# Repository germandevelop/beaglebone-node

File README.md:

# beaglebone-node
## Build
### Release ###
```
mkdir ./build
cd ./build
cmake ..
make all
```
### Debug ###
```
mkdir ./build
cd ./build
cmake -DCMAKE_BUILD_TYPE=Debug ..
make all
```
## Build tests
### Build ###
```
mkdir ./build
cd ./build
cmake -DCMAKE_BUILD_TYPE=Debug -DBUILD_TESTS=ON ..
make tests
```
### Run ###
```
make test
```

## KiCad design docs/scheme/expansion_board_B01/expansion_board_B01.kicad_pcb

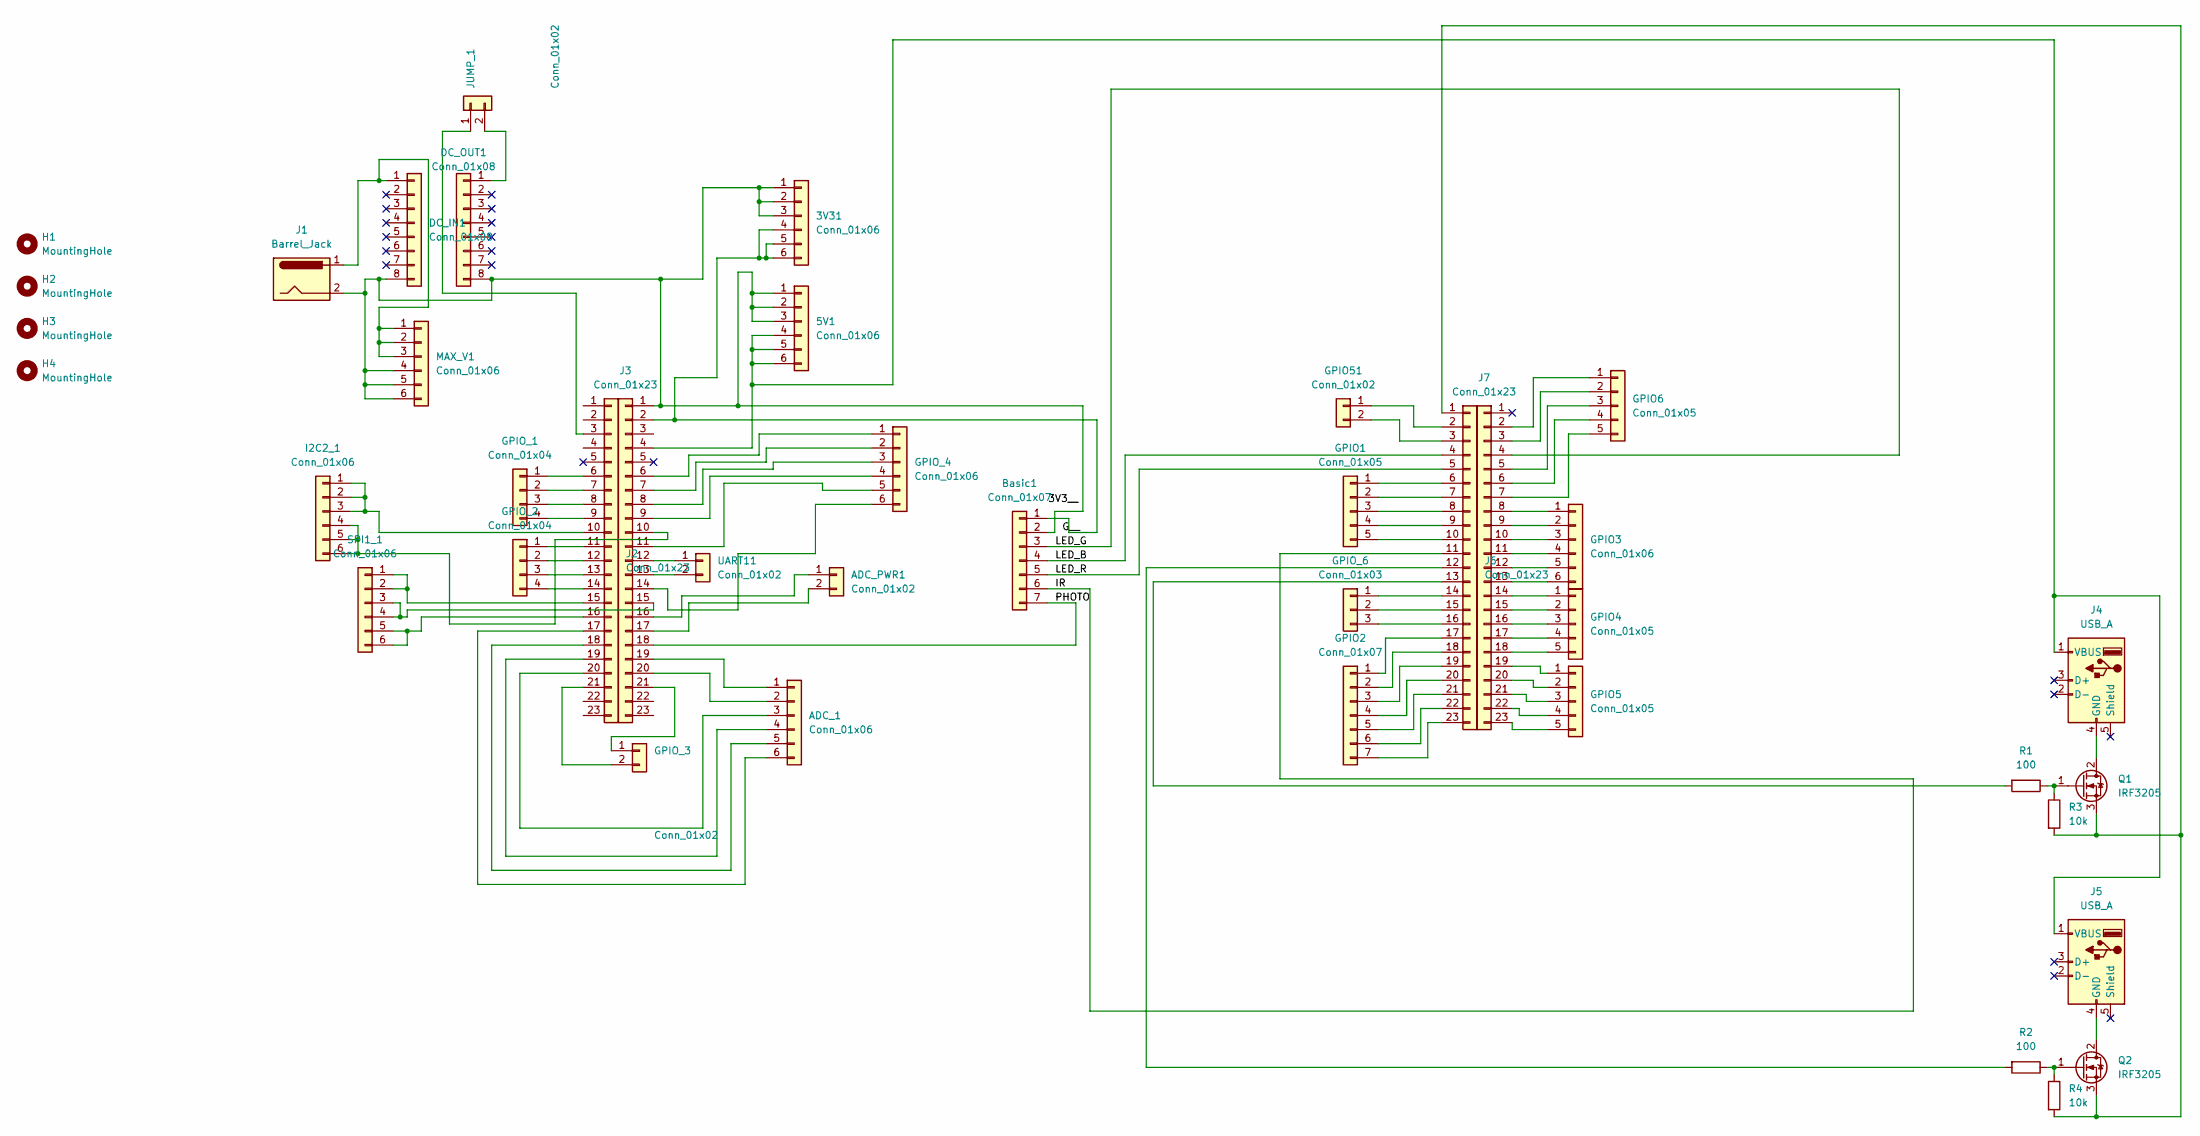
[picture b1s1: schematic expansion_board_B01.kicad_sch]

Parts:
3V31, 5V1: Conn_01x06; PinHeader_1x06_P2.54mm_Vertical
ADC_1: Conn_01x06; PinHeader_1x06_P2.54mm_Vertical
ADC_PWR1: Conn_01x02; PinHeader_1x02_P2.54mm_Vertical
Basic1: Conn_01x07; PinHeader_1x07_P2.54mm_Vertical
DC_IN1: Conn_01x08; PinHeader_1x08_P2.54mm_Vertical
DC_OUT1: Conn_01x08; PinHeader_1x08_P2.54mm_Vertical
GPIO1, GPIO4, GPIO5, GPIO6: Conn_01x05; PinHeader_1x05_P2.54mm_Vertical
GPIO2: Conn_01x07; PinHeader_1x07_P2.54mm_Vertical
GPIO3: Conn_01x06; PinHeader_1x06_P2.54mm_Vertical
GPIO51: Conn_01x02; PinHeader_1x02_P2.54mm_Vertical
GPIO_1, GPIO_2: Conn_01x04; PinHeader_1x04_P2.54mm_Vertical
GPIO_3: Conn_01x02; PinHeader_1x02_P2.54mm_Vertical
GPIO_4: Conn_01x06; PinHeader_1x06_P2.54mm_Vertical
GPIO_6: Conn_01x03; PinHeader_1x03_P2.54mm_Vertical
H1, H2, H3, H4: MountingHole; MountingHole_2.5mm_Pad
I2C2_1: Conn_01x06; PinHeader_1x06_P2.54mm_Vertical
J1: Barrel_Jack; BarrelJack_Horizontal
J2, J3, J6, J7: Conn_01x23; PinHeader_1x23_P2.54mm_Vertical
J4, J5: USB_A; USB_A_CONNFLY_DS1095-WNR0
JUMP_1: Conn_01x02; PinHeader_1x02_P2.54mm_Vertical
MAX_V1: Conn_01x06; PinHeader_1x06_P2.54mm_Vertical
Q1, Q2: IRF3205; TO-220-3_Vertical
R1, R2: 100; R_Axial_DIN0207_L6.3mm_D2.5mm_P10.16mm_Horizontal
R3, R4: 10k; R_Axial_DIN0207_L6.3mm_D2.5mm_P10.16mm_Horizontal
SPI1_1: Conn_01x06; PinHeader_1x06_P2.54mm_Vertical
UART11: Conn_01x02; PinHeader_1x02_P2.54mm_Vertical

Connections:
/IR: Basic1.6, J6.11
/LED_B: Basic1.4, J6.4
/LED_G: Basic1.3, J7.4
/LED_R: Basic1.5, J6.5
/PHOTO: Basic1.7, J3.18
unnamed: 3V31.1, 3V31.2, 3V31.3, 5V1.1, 5V1.2, 5V1.3, Basic1.2, DC_IN1.8, DC_OUT1.8, J1.2, J3.1, MAX_V1.4, MAX_V1.5, MAX_V1.6
unnamed: 3V31.4, 3V31.5, 3V31.6, Basic1.1, J3.2
unnamed: 5V1.4, 5V1.5, 5V1.6, J3.4, J4.1 (VBUS), J5.1 (VBUS)
unnamed: ADC_1.1, J3.19
unnamed: ADC_1.2, J3.20
unnamed: ADC_1.3, J2.20
unnamed: ADC_1.4, J2.19
unnamed: ADC_1.5, J2.18
unnamed: ADC_1.6, J2.17
unnamed: ADC_PWR1.1, J3.16
unnamed: ADC_PWR1.2, J3.17
unnamed: DC_IN1.1, J1.1, MAX_V1.1, MAX_V1.2, MAX_V1.3
unnamed: DC_OUT1.1, JUMP_1.2
unnamed: GPIO1.1, J6.6
unnamed: GPIO1.2, J6.7
unnamed: GPIO1.3, J6.8
unnamed: GPIO1.4, J6.9
unnamed: GPIO1.5, J6.10
unnamed: GPIO2.1, J6.17
unnamed: GPIO2.2, J6.18
unnamed: GPIO2.3, J6.19
unnamed: GPIO2.4, J6.20
unnamed: GPIO2.5, J6.21
unnamed: GPIO2.6, J6.22
unnamed: GPIO2.7, J6.23
unnamed: GPIO3.1, J7.8
unnamed: GPIO3.2, J7.9
unnamed: GPIO3.3, J7.10
unnamed: GPIO3.4, J7.11
unnamed: GPIO3.5, J7.12
unnamed: GPIO3.6, J7.13
unnamed: GPIO4.1, J7.14
unnamed: GPIO4.2, J7.15
unnamed: GPIO4.3, J7.16
unnamed: GPIO4.4, J7.17
unnamed: GPIO4.5, J7.18
unnamed: GPIO5.1, J7.19
unnamed: GPIO5.2, J7.20
unnamed: GPIO5.3, J7.21
unnamed: GPIO5.4, J7.22
unnamed: GPIO5.5, J7.23
unnamed: GPIO6.1, J7.2
unnamed: GPIO6.2, J7.3
unnamed: GPIO6.3, J7.5
unnamed: GPIO6.4, J7.6
unnamed: GPIO6.5, J7.7
unnamed: GPIO51.1, J6.2
unnamed: GPIO51.2, J6.3
unnamed: GPIO_1.1, J2.6
unnamed: GPIO_1.2, J2.7
unnamed: GPIO_1.3, J2.8
unnamed: GPIO_1.4, J2.9
unnamed: GPIO_2.1, J2.11
unnamed: GPIO_2.2, J2.12
unnamed: GPIO_2.3, J2.13
unnamed: GPIO_2.4, J2.14
unnamed: GPIO_3.1, J3.21
unnamed: GPIO_3.2, J2.21
unnamed: GPIO_4.1, J3.6
unnamed: GPIO_4.2, J3.7
unnamed: GPIO_4.3, J3.8
unnamed: GPIO_4.4, J3.9
unnamed: GPIO_4.5, J3.11
unnamed: GPIO_4.6, J3.14
unnamed: GPIO_6.1, J6.14
unnamed: GPIO_6.2, J6.15
unnamed: GPIO_6.3, J6.16
unnamed: I2C2_1.1, I2C2_1.2, I2C2_1.3, J2.10
unnamed: I2C2_1.4, I2C2_1.5, I2C2_1.6, J3.10
unnamed: J2.3, JUMP_1.1
unnamed: J2.15, SPI1_1.1, SPI1_1.2
unnamed: J2.16, SPI1_1.5, SPI1_1.6
unnamed: J3.12, UART11.1
unnamed: J3.13, UART11.2
unnamed: J3.15, SPI1_1.3, SPI1_1.4
unnamed: J4.4 (GND), Q1.2 (D)
unnamed: J5.4 (GND), Q2.2 (D)
unnamed: J6.1, Q1.3 (S), Q2.3 (S), R3.2, R4.2
unnamed: J6.12, R2.2
unnamed: J6.13, R1.2
unnamed: Q1.1 (G), R1.1, R3.1
unnamed: Q2.1 (G), R2.1, R4.1

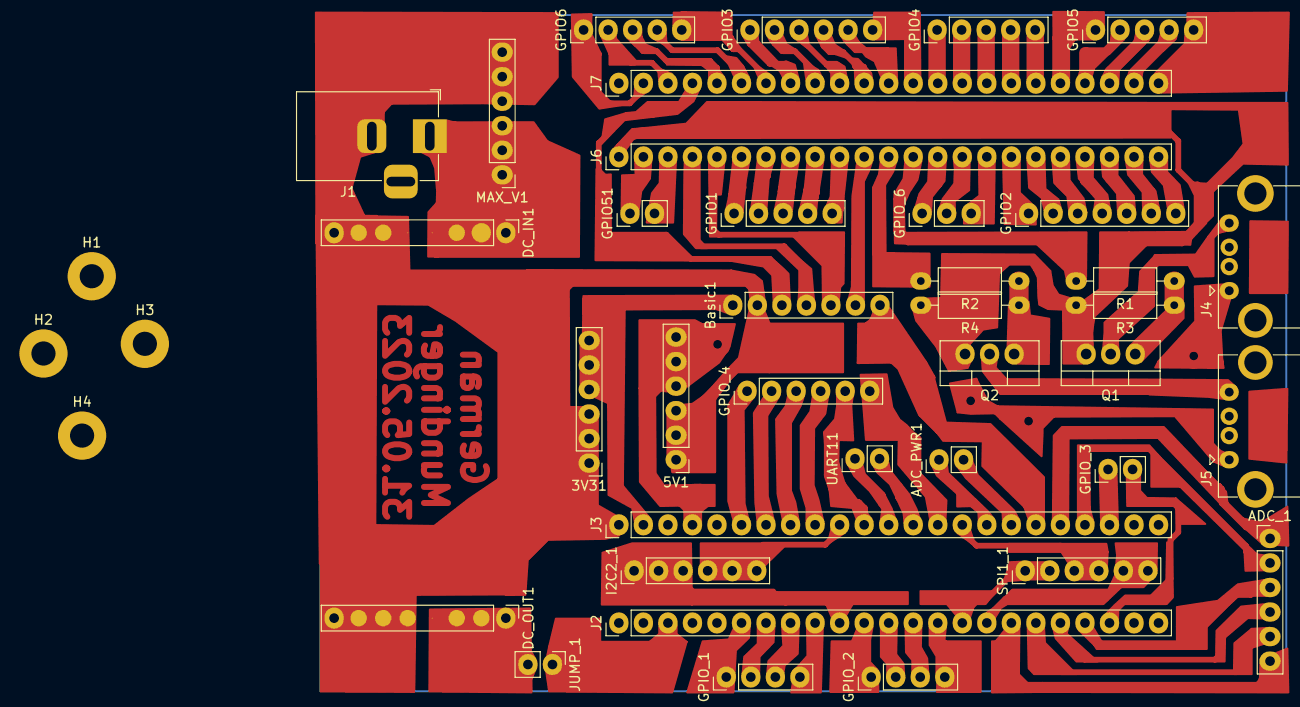
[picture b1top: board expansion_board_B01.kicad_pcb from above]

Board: 2 copper layers, 41 parts (0 on the bottom side), 87 nets.

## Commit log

2024-02-03 Initial
2024-02-04 Fix something
2024-02-25 Improve cmake
2024-03-05 Refactor board
2024-03-18 Add B01 node
2024-03-18 Add FreeBSD support
2024-03-20 Make backup
2024-03-20 Backup TCP
2024-03-20 Refactor TCp
2024-03-21 Start node server
2024-03-21 Add node server
2024-03-22 Add options
2024-03-24 Refactor TCP coroutines
2024-03-25 Refactor coroutines
2024-03-26 Add configuration file
2024-04-12 Completeboards
2024-04-20 Fix server broadcast
2024-04-23 Add version response
2024-06-04 Pre-release 0.1.0
